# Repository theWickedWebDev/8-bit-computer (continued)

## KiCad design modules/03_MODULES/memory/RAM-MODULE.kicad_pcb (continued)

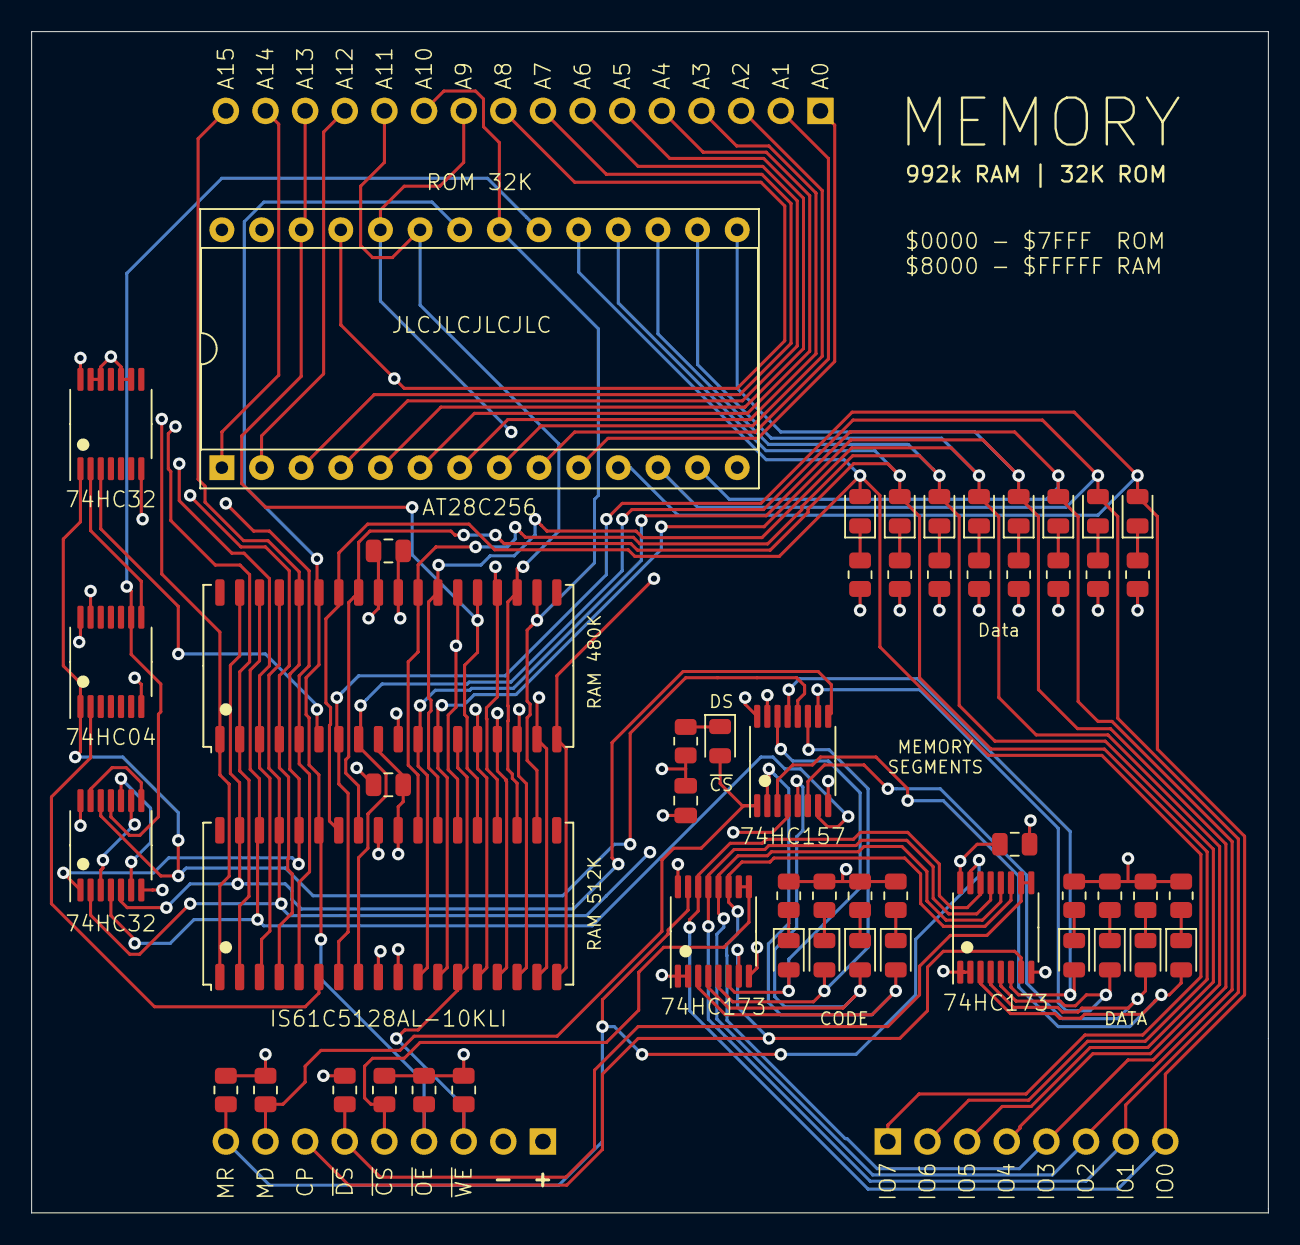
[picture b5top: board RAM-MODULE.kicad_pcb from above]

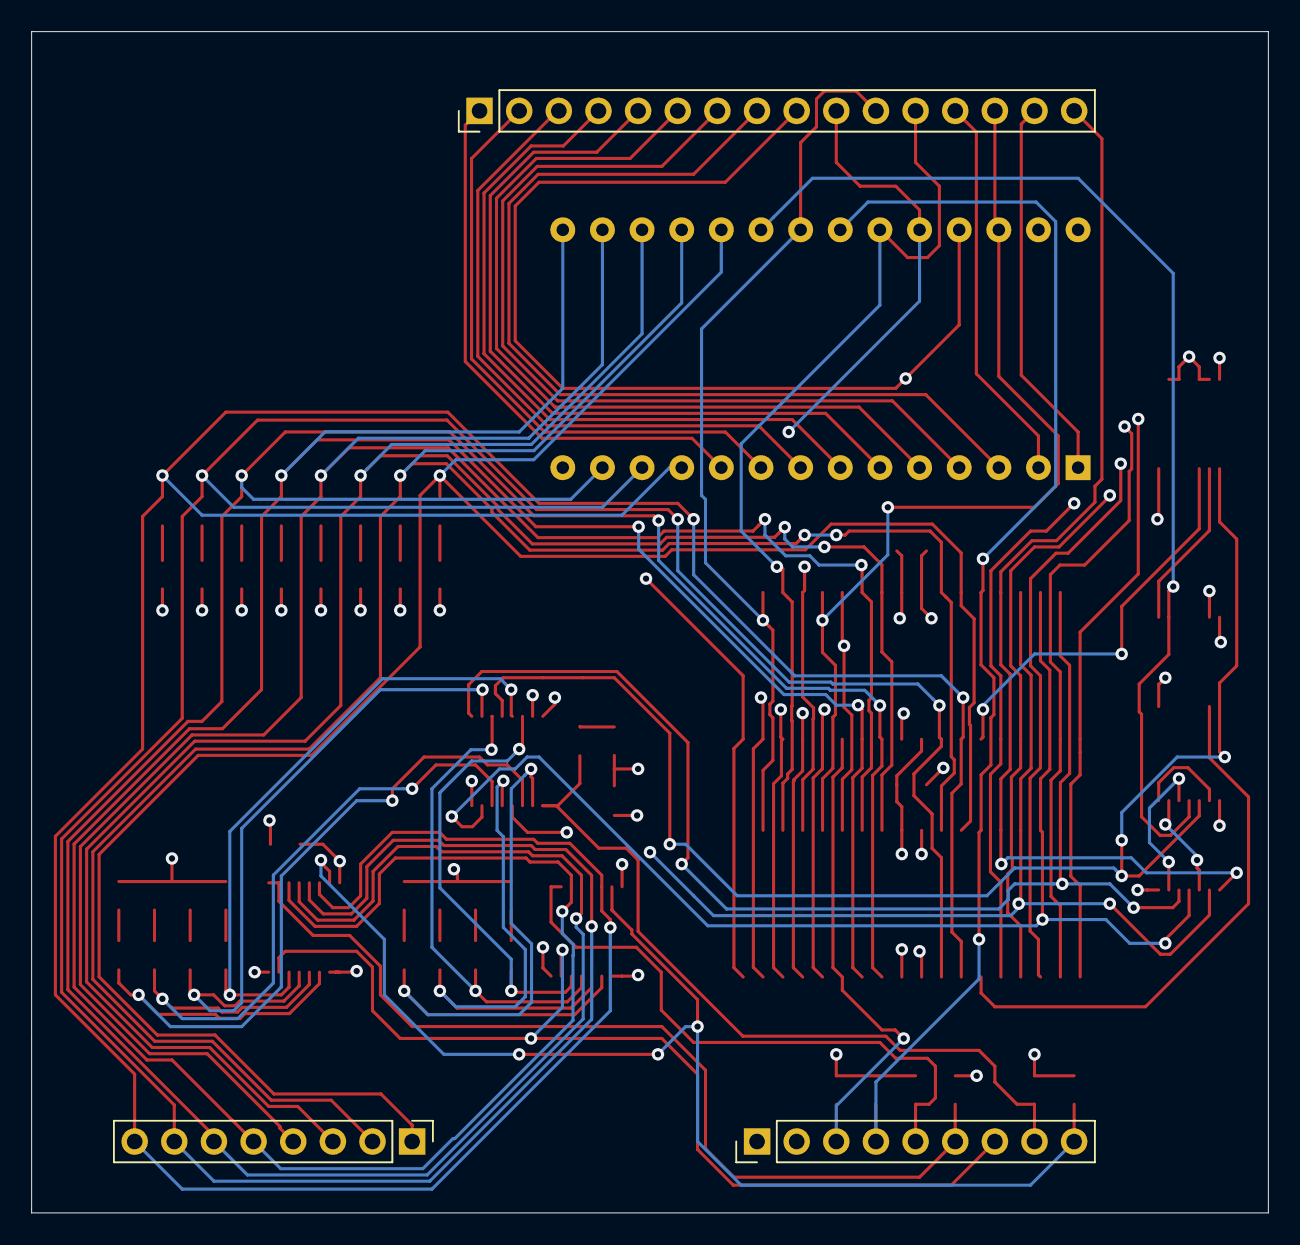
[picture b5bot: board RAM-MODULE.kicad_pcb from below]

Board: 4 copper layers, 79.2 x 75.7 mm, 56 parts (3 on the bottom side), 69 nets.

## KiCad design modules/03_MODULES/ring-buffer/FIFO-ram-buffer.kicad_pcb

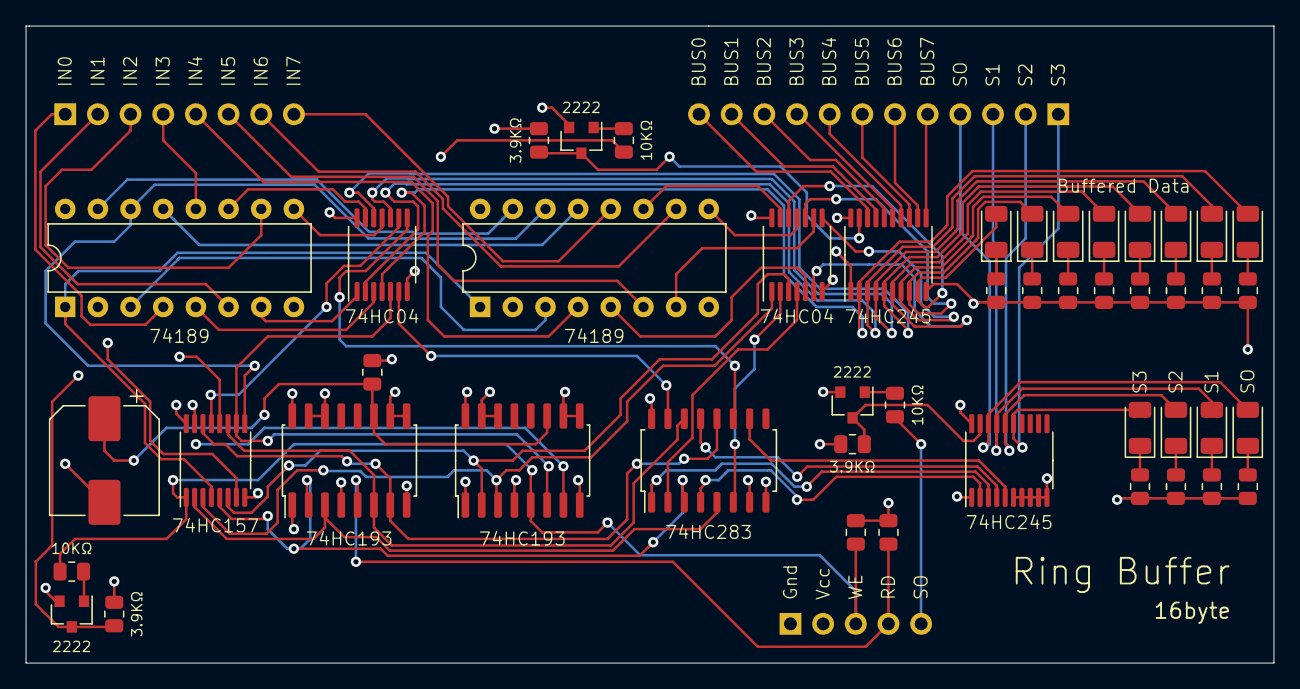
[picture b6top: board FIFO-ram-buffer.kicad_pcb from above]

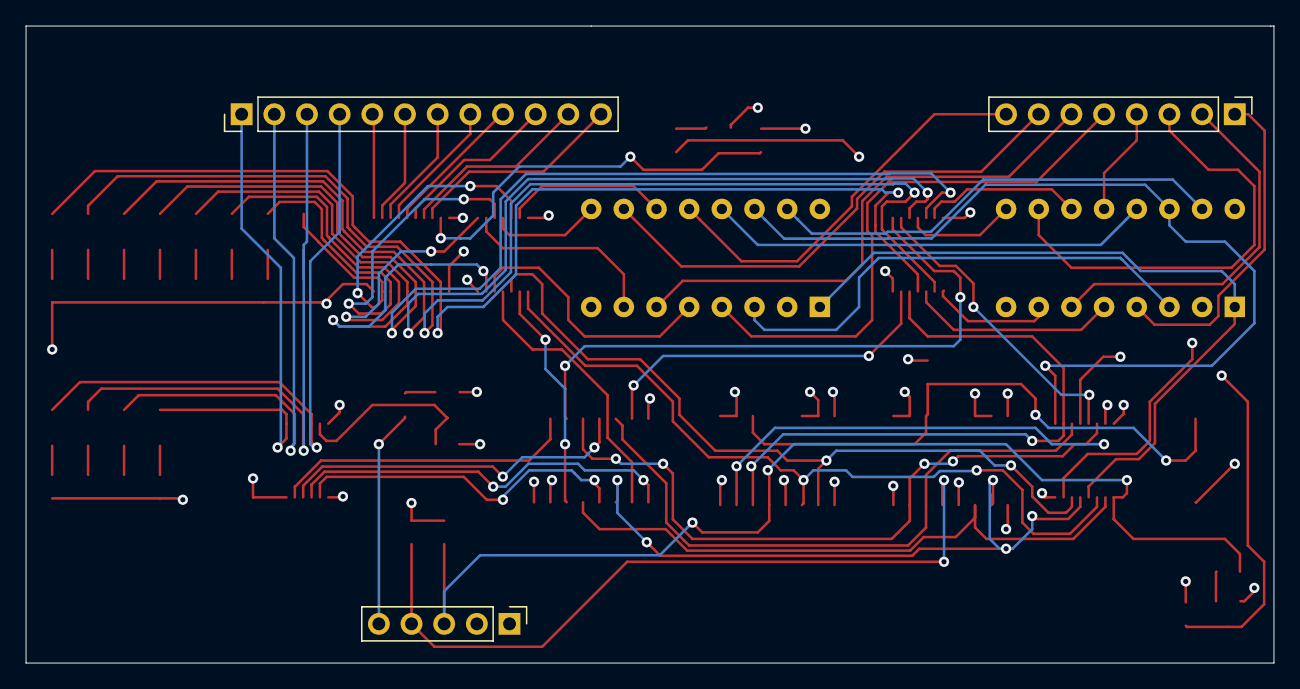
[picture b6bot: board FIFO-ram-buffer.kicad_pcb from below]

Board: 4 copper layers, 97.0 x 49.5 mm, 50 parts (3 on the bottom side), 80 nets.

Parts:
C1: C; CP_Elec_8x10
D1, D2, D3, D4, D5, D6, D7, D8, D9, D10, D11, D12: LED; LED_1206_3216Metric
J1: Conn_01x05; PinHeader_1x05_P2.54mm_Vertical
J2: Conn_01x08; PinHeader_1x08_P2.54mm_Vertical
J3: Conn_01x12; PinHeader_1x12_P2.54mm_Vertical
Q1, Q2, Q3: PMBT2222; SOT-23
R1, R6, R7: 10kohm; R_0805_2012Metric
R2, R8, R9: 3.9kohm; R_0805_2012Metric
R3, R4, R5, R10, R11, R12, R13, R14, R15, R16, R17, R18, R19, R20, R21: 1kohm; R_0805_2012Metric
U1, U2: 74LS04; TSSOP-14_4.4x5mm_P0.65mm
U3: 74HC157PW,118; TSSOP-16_4.4x5mm_P0.65mm
U4, U6: 74LS193; SO-16_5.3x10.2mm_P1.27mm
U5, U7: 74189; DIP-16_W7.62mm
U8: 74LS283; SOIC-16_4.55x10.3mm_P1.27mm
U9, U10: 74HC245; TSSOP-20_4.4x6.5mm_P0.65mm

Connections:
BUS0: J3.12, U10.18
BUS1: J3.11, U10.17
BUS2: J3.10, U10.16
BUS3: J3.9, U10.15
BUS4: J3.8, U10.14
BUS5: J3.7, U10.13
BUS6: J3.6, U10.12
BUS7: J3.5, U10.11
DATACOUNT0: U8.4, U9.2
DATACOUNT1: U8.1, U9.3
DATACOUNT2: U8.13, U9.4
DATACOUNT3: U8.10, U9.5
GND: C1.2, J1.1, Q1.2, Q2.2, Q3.2, R3.2, R4.2, R10.2, R11.2, R12.2, R13.2, R14.2, R15.2, R16.2, R17.2, R18.2, R19.2, R20.2, R21.2, U1.7, U2.7, U3.8, U3.15, U4.1, U4.8, U4.9, U4.10, U4.14, U4.15, U5.2, U5.8, U6.1, U6.8, U6.9, U6.10, U6.14, U6.15, U7.2, U7.8, U8.8, U9.6, U9.7, U9.8, U9.9, U9.10, U10.10
INPUT0: J2.1, U5.4
INPUT1: J2.2, U5.6
INPUT2: J2.3, U5.10
INPUT3: J2.4, U5.12
INPUT4: J2.5, U7.4
INPUT5: J2.6, U7.6
INPUT6: J2.7, U7.10
INPUT7: J2.8, U7.12
unnamed: C1.1, R5.2, U4.11, U6.11
unnamed: D1.1, R10.1
unnamed: D2.1, R11.1
unnamed: D3.1, R12.1
unnamed: D4.1, R13.1
unnamed: D5.1, R14.1
unnamed: D6.1, R15.1
unnamed: D7.1, R16.1
unnamed: D8.1, R17.1
unnamed: D9.1, R18.1
unnamed: D10.1, R19.1
unnamed: D11.1, R20.1
unnamed: D12.1, R21.1
unnamed: Q1.1, R1.2
unnamed: Q2.1, R6.2
unnamed: Q2.3, R8.1, U9.19
unnamed: Q3.1, R7.2
unnamed: Q3.3, R9.1, U10.19
unnamed: U1.1, U5.7
unnamed: U1.3, U5.5
unnamed: U1.6, U8.15
unnamed: U1.8, U8.11
unnamed: U1.11, U5.9
unnamed: U1.13, U5.11
unnamed: U2.2, U8.6
unnamed: U2.4, U8.2
unnamed: U2.5, U7.5
unnamed: U2.9, U7.7
unnamed: U2.11, U7.9
unnamed: U2.13, U7.11
unnamed: U3.4, U5.1, U7.1
unnamed: U3.7, U5.15, U7.15
unnamed: U3.9, U5.14, U7.14
unnamed: U3.12, U5.13, U7.13
OUTPUT_STATUS: J1.5, R6.1
R0: U3.2, U4.3, U8.5
R1: U3.5, U4.2, U8.3
R2: U3.11, U4.6, U8.14
R3: U3.14, U4.7, U8.12
RAM0: D12.2, U1.4, U10.2
RAM1: D11.2, U1.2, U10.3
RAM2: D10.2, U1.10, U10.4
RAM3: D9.2, U1.12, U10.5
RAM4: D8.2, U2.6, U10.6
RAM5: D7.2, U2.8, U10.7
RAM6: D5.2, U2.10, U10.8
RAM7: D3.2, U2.12, U10.9
READ: J1.4, R3.1, R7.1, U4.5
STATUS0: D1.2, J3.4, U9.18
STATUS1: D2.2, J3.3, U9.17
STATUS2: D4.2, J3.2, U9.16
STATUS3: D6.2, J3.1, U9.15
VCC: J1.2, R2.2, R5.1, R8.2, R9.2, U1.14, U2.14, U3.16, U4.4, U4.16, U5.16, U6.4, U6.16, U7.16, U8.7, U8.16, U9.1, U9.20, U10.1, U10.20
W0: U2.1, U3.3, U6.3
W1: U2.3, U3.6, U6.2
W2: U1.5, U3.10, U6.6
W3: U1.9, U3.13, U6.7
WRITE: J1.3, R1.1, R4.1, U3.1, U6.5
~WE: Q1.3, R2.1, U5.3, U7.3

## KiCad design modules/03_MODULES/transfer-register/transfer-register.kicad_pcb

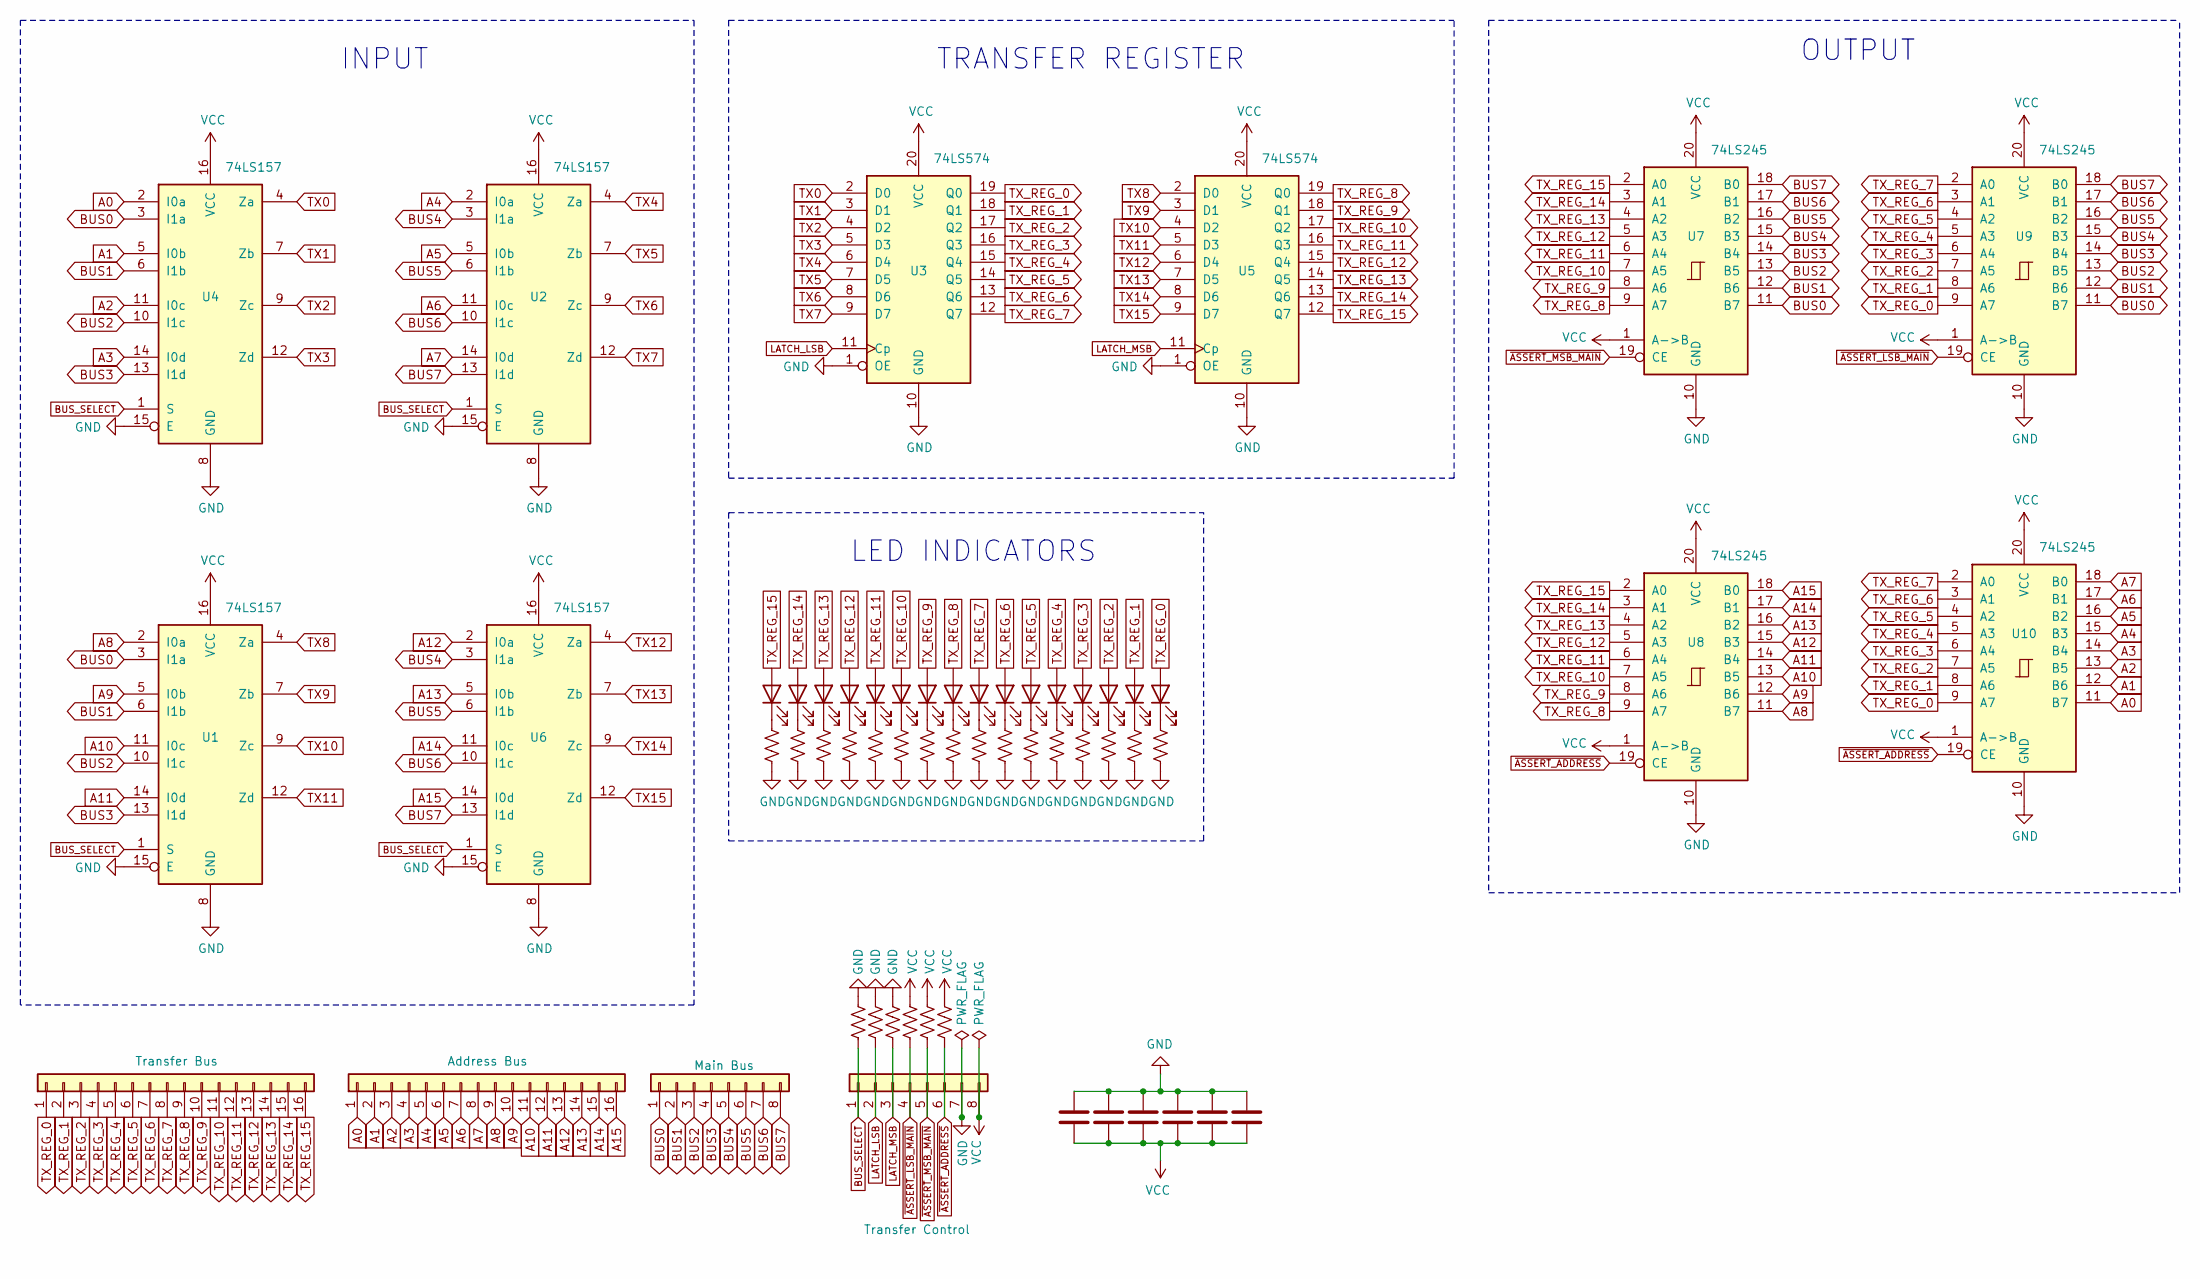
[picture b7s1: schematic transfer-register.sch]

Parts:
C1, C2, C3, C4, C5, C6: C; C_0805_2012Metric
D1, D2, D3, D4, D5, D6, D7, D8, D9, D10, D11, D12, D13, D14, D15, D16: LED; LED_0805_2012Metric
J1, J2: Conn_01x16; PinHeader_1x16_P2.54mm_Vertical
J3, J4: Conn_01x08; PinHeader_1x08_P2.54mm_Vertical
R1, R2, R3, R4, R5, R6, R7, R8, R9, R10, R11, R12, R13, R14, R15, R16, R17, R18, R19, R20, R21, R22: R_US; R_0805_2012Metric
U1, U2, U4, U6: 74LS157; TSSOP-16_4.4x5mm_P0.65mm
U3, U5: 74LS574; SO-20_5.3x12.6mm_P1.27mm
U7, U8, U9, U10: 74LS245; TSSOP-20_4.4x6.5mm_P0.65mm

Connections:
A0: J2.1, U4.2 (I0a), U10.11 (B7)
A1: J2.2, U4.5 (I0b), U10.12 (B6)
A2: J2.3, U4.11 (I0c), U10.13 (B5)
A3: J2.4, U4.14 (I0d), U10.14 (B4)
A4: J2.5, U2.2 (I0a), U10.15 (B3)
A5: J2.6, U2.5 (I0b), U10.16 (B2)
A6: J2.7, U2.11 (I0c), U10.17 (B1)
A7: J2.8, U2.14 (I0d), U10.18 (B0)
A8: J2.9, U1.2 (I0a), U8.11 (B7)
A9: J2.10, U1.5 (I0b), U8.12 (B6)
A10: J2.11, U1.11 (I0c), U8.13 (B5)
A11: J2.12, U1.14 (I0d), U8.14 (B4)
A12: J2.13, U6.2 (I0a), U8.15 (B3)
A13: J2.14, U6.5 (I0b), U8.16 (B2)
A14: J2.15, U6.11 (I0c), U8.17 (B1)
A15: J2.16, U6.14 (I0d), U8.18 (B0)
BUS0: J3.1, U1.3 (I1a), U4.3 (I1a), U7.11 (B7), U9.11 (B7)
BUS1: J3.2, U1.6 (I1b), U4.6 (I1b), U7.12 (B6), U9.12 (B6)
BUS2: J3.3, U1.10 (I1c), U4.10 (I1c), U7.13 (B5), U9.13 (B5)
BUS3: J3.4, U1.13 (I1d), U4.13 (I1d), U7.14 (B4), U9.14 (B4)
BUS4: J3.5, U2.3 (I1a), U6.3 (I1a), U7.15 (B3), U9.15 (B3)
BUS5: J3.6, U2.6 (I1b), U6.6 (I1b), U7.16 (B2), U9.16 (B2)
BUS6: J3.7, U2.10 (I1c), U6.10 (I1c), U7.17 (B1), U9.17 (B1)
BUS7: J3.8, U2.13 (I1d), U6.13 (I1d), U7.18 (B0), U9.18 (B0)
BUS_SELECT: J4.1, R17.2, U1.1 (S), U2.1 (S), U4.1 (S), U6.1 (S)
GND: C1.2, C2.2, C3.2, C4.2, C5.2, C6.2, J4.7, R1.2, R2.2, R3.2, R4.2, R5.2, R6.2, R7.2, R8.2, R9.2, R10.2, R11.2, R12.2, R13.2, R14.2, R15.2, R16.2, R17.1, R18.1, R19.1, U1.8 (GND), U1.15 (E), U2.8 (GND), U2.15 (E), U3.1 (OE), U3.10 (GND), U4.8 (GND), U4.15 (E), U5.1 (OE), U5.10 (GND), U6.8 (GND), U6.15 (E), U7.10 (GND), U8.10 (GND), U9.10 (GND), U10.10 (GND)
LATCH_LSB: J4.2, R18.2, U3.11 (Cp)
LATCH_MSB: J4.3, R19.2, U5.11 (Cp)
unnamed: D1.1 (K), R1.1
unnamed: D2.1 (K), R2.1
unnamed: D3.1 (K), R3.1
unnamed: D4.1 (K), R4.1
unnamed: D5.1 (K), R5.1
unnamed: D6.1 (K), R6.1
unnamed: D7.1 (K), R7.1
unnamed: D8.1 (K), R8.1
unnamed: D9.1 (K), R9.1
unnamed: D10.1 (K), R10.1
unnamed: D11.1 (K), R11.1
unnamed: D12.1 (K), R12.1
unnamed: D13.1 (K), R13.1
unnamed: D14.1 (K), R14.1
unnamed: D15.1 (K), R15.1
unnamed: D16.1 (K), R16.1
TX0: U3.2 (D0), U4.4 (Za)
TX1: U3.3 (D1), U4.7 (Zb)
TX2: U3.4 (D2), U4.9 (Zc)
TX3: U3.5 (D3), U4.12 (Zd)
TX4: U2.4 (Za), U3.6 (D4)
TX5: U2.7 (Zb), U3.7 (D5)
TX6: U2.9 (Zc), U3.8 (D6)
TX7: U2.12 (Zd), U3.9 (D7)
TX8: U1.4 (Za), U5.2 (D0)
TX9: U1.7 (Zb), U5.3 (D1)
TX10: U1.9 (Zc), U5.4 (D2)
TX11: U1.12 (Zd), U5.5 (D3)
TX12: U5.6 (D4), U6.4 (Za)
TX13: U5.7 (D5), U6.7 (Zb)
TX14: U5.8 (D6), U6.9 (Zc)
TX15: U5.9 (D7), U6.12 (Zd)
TX_REG_0: D16.2 (A), J1.1, U3.19 (Q0), U9.9 (A7), U10.9 (A7)
TX_REG_1: D15.2 (A), J1.2, U3.18 (Q1), U9.8 (A6), U10.8 (A6)
TX_REG_2: D14.2 (A), J1.3, U3.17 (Q2), U9.7 (A5), U10.7 (A5)
TX_REG_3: D13.2 (A), J1.4, U3.16 (Q3), U9.6 (A4), U10.6 (A4)
TX_REG_4: D12.2 (A), J1.5, U3.15 (Q4), U9.5 (A3), U10.5 (A3)
TX_REG_5: D11.2 (A), J1.6, U3.14 (Q5), U9.4 (A2), U10.4 (A2)
TX_REG_6: D10.2 (A), J1.7, U3.13 (Q6), U9.3 (A1), U10.3 (A1)
TX_REG_7: D9.2 (A), J1.8, U3.12 (Q7), U9.2 (A0), U10.2 (A0)
TX_REG_8: D8.2 (A), J1.9, U5.19 (Q0), U7.9 (A7), U8.9 (A7)
TX_REG_9: D7.2 (A), J1.10, U5.18 (Q1), U7.8 (A6), U8.8 (A6)
TX_REG_10: D6.2 (A), J1.11, U5.17 (Q2), U7.7 (A5), U8.7 (A5)
TX_REG_11: D5.2 (A), J1.12, U5.16 (Q3), U7.6 (A4), U8.6 (A4)
TX_REG_12: D4.2 (A), J1.13, U5.15 (Q4), U7.5 (A3), U8.5 (A3)
TX_REG_13: D3.2 (A), J1.14, U5.14 (Q5), U7.4 (A2), U8.4 (A2)
TX_REG_14: D2.2 (A), J1.15, U5.13 (Q6), U7.3 (A1), U8.3 (A1)
TX_REG_15: D1.2 (A), J1.16, U5.12 (Q7), U7.2 (A0), U8.2 (A0)
VCC: C1.1, C2.1, C3.1, C4.1, C5.1, C6.1, J4.8, R20.1, R21.1, R22.1, U1.16 (VCC), U2.16 (VCC), U3.20 (VCC), U4.16 (VCC), U5.20 (VCC), U6.16 (VCC), U7.1 (A->B), U7.20 (VCC), U8.1 (A->B), U8.20 (VCC), U9.1 (A->B), U9.20 (VCC), U10.1 (A->B), U10.20 (VCC)
~ASSERT_ADDRESS: J4.6, R22.2, U8.19 (CE), U10.19 (CE)
~ASSERT_LSB_MAIN: J4.4, R20.2, U9.19 (CE)
~ASSERT_MSB_MAIN: J4.5, R21.2, U7.19 (CE)

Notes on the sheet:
INPUT
TRANSFER REGISTER
OUTPUT
LED INDICATORS

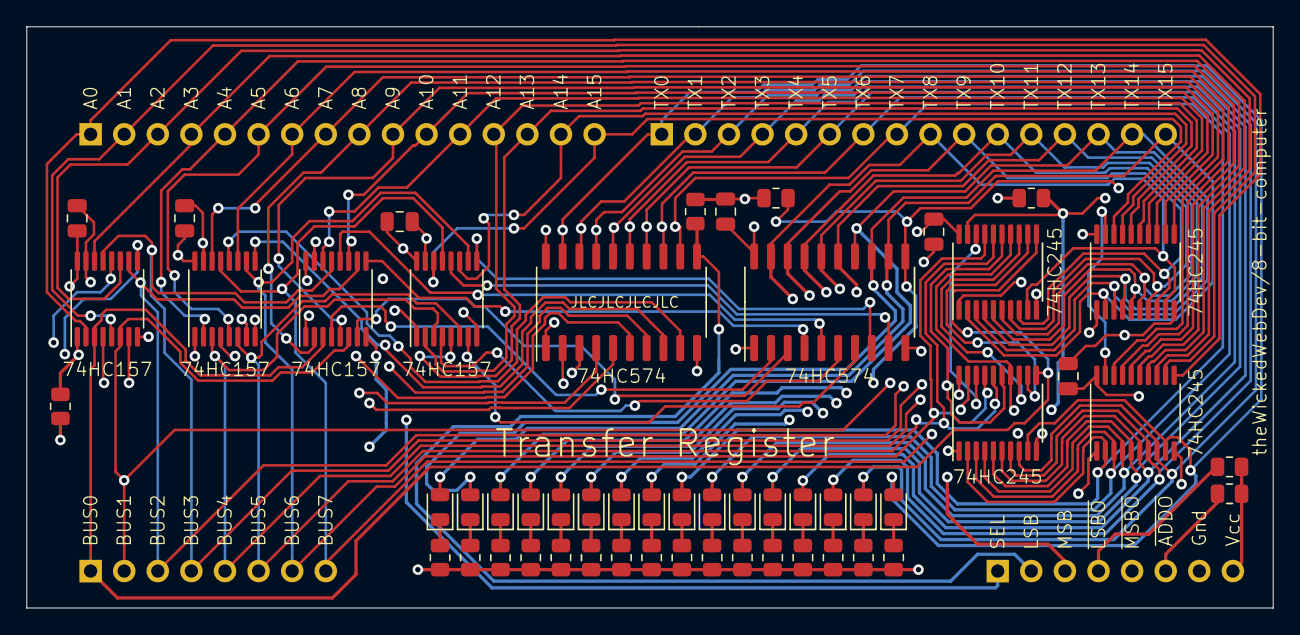
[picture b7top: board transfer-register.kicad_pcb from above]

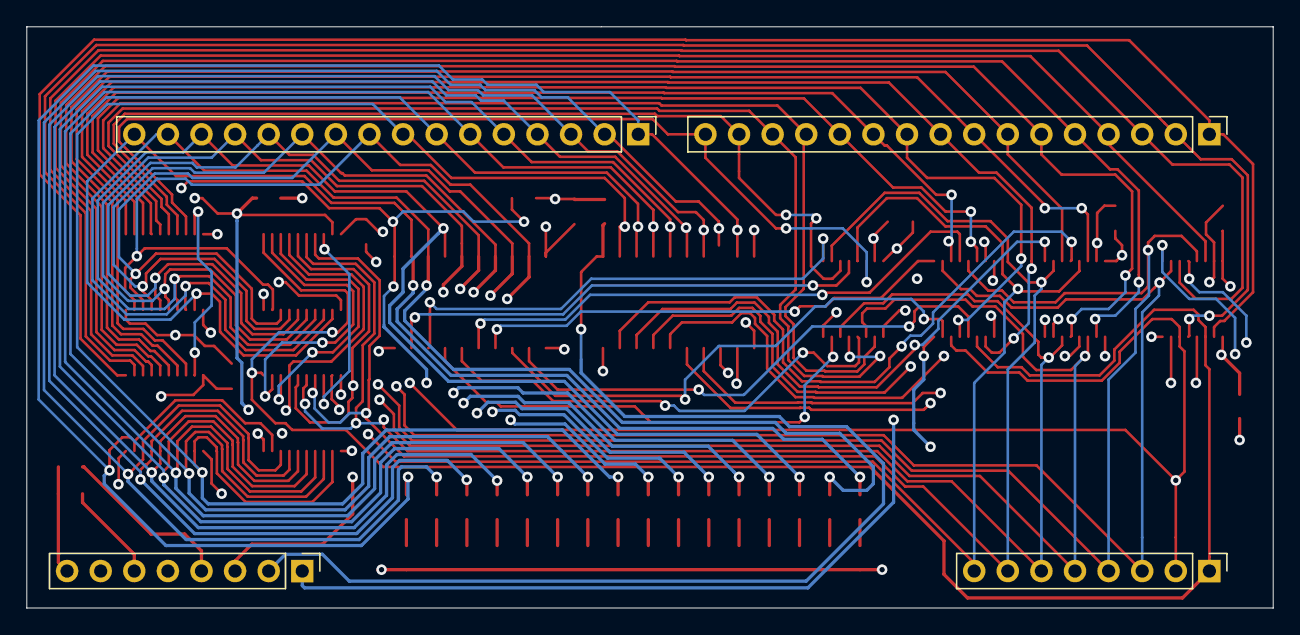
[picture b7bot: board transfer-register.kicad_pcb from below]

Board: 4 copper layers, 94.2 x 43.9 mm, 58 parts (4 on the bottom side), 80 nets.
